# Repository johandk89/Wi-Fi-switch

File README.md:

# ESP8266 Wi-Fi plug
ESP8266 Wi-Fi plug eagle schematic

##Overview
This is the intial design of a ESP8266 relay switch. 
The ESP will draw its power from a 220v to 5v power module (Still need to find the perfect one)
This relay switch is heavliy based on : 

###Parts list
1 x ESP8266 E01
1 x Relay
2 x R1 Resistor
1 x LED
1 x Transistor
1 x Resistor

###License
The MIT License (MIT)

Copyright (c) 2015 johandk89

Permission is hereby granted, free of charge, to any person obtaining a copy
of this software and associated documentation files (the "Software"), to deal
in the Software without restriction, including without limitation the rights
to use, copy, modify, merge, publish, distribute, sublicense, and/or sell
copies of the Software, and to permit persons to whom the Software is
furnished to do so, subject to the following conditions:

The above copyright notice and this permission notice shall be included in all
copies or substantial portions of the Software.

THE SOFTWARE IS PROVIDED "AS IS", WITHOUT WARRANTY OF ANY KIND, EXPRESS OR
IMPLIED, INCLUDING BUT NOT LIMITED TO THE WARRANTIES OF MERCHANTABILITY,
FITNESS FOR A PARTICULAR PURPOSE AND NONINFRINGEMENT. IN NO EVENT SHALL THE
AUTHORS OR COPYRIGHT HOLDERS BE LIABLE FOR ANY CLAIM, DAMAGES OR OTHER
LIABILITY, WHETHER IN AN ACTION OF CONTRACT, TORT OR OTHERWISE, ARISING FROM,
OUT OF OR IN CONNECTION WITH THE SOFTWARE OR THE USE OR OTHER DEALINGS IN THE
SOFTWARE.

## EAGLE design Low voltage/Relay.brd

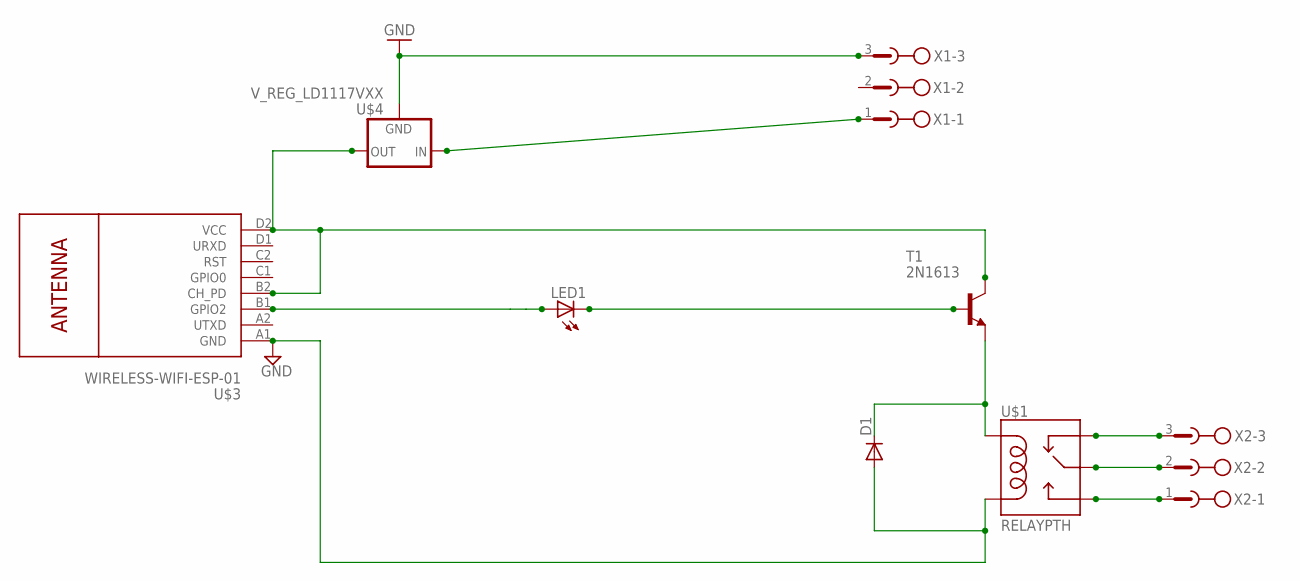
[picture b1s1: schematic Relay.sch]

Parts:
D1: DIODE-D-2.5; D-2.5
LED1: LED3MM
T1: 2N1613; TO5
U$1: RELAYPTH; SRD-05VDC-SL-C
U$3: WIRELESS-WIFI-ESP-01
U$4: V_REG_LD1117VXX; 78XXL
X1, X2: W232-3

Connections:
GND: D1.A, U$1.COIL0, U$3.A1 (GND), U$4.IN (GND), X1.3
unnamed: T1.3 (C), U$3.B2 (CH_PD), U$3.D2 (VCC), U$4.GND (OUT)
unnamed: LED1.A, U$3.B1 (GPIO2)
unnamed: U$4.OUT (IN), X1.1
unnamed: LED1.K (C), T1.2 (B)
unnamed: U$1.SWCLOSED (SWCLOSE), X2.3
unnamed: D1.C, T1.1 (E), U$1.COIL1
unnamed: U$1.SWCOMMON, X2.2
unnamed: U$1.SWOPEN, X2.1

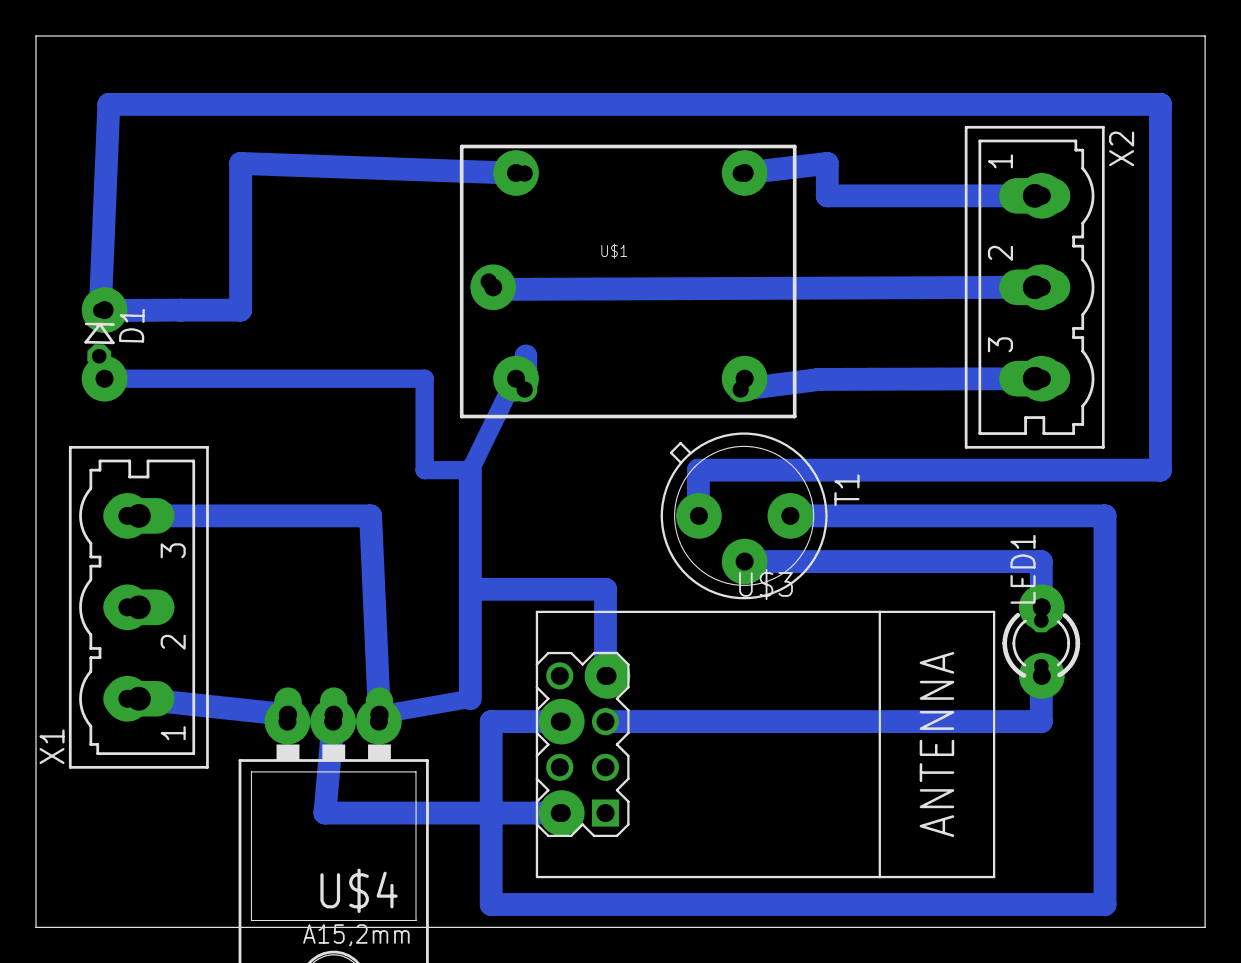
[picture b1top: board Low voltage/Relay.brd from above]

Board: 2 copper layers, 65.0 x 49.5 mm, 8 parts (0 on the bottom side), 9 nets.

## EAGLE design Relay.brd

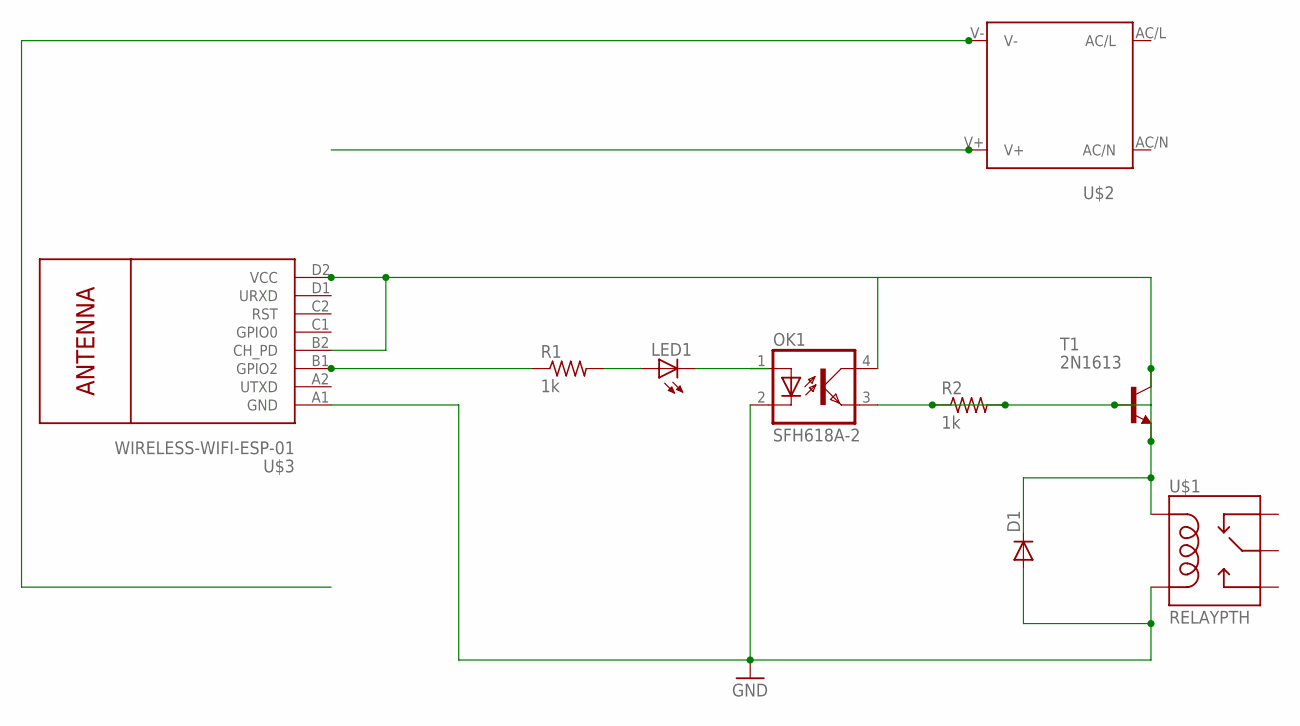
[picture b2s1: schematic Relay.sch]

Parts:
D1: DIODE-D-2.5; D-2.5
LED1: LED3MM
OK1: SFH618A-2; DIP4
R1, R2: 1k; R2012
T1: 2N1613; TO5
U$1: RELAYPTH; SRD-05VDC-SL-C
U$2: IRM_15/20
U$3: WIRELESS-WIFI-ESP-01

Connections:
GND: D1.A, OK1.2 (C), U$1.COIL0, U$3.A1 (GND)
unnamed: R1.1, U$3.B1 (GPIO2)
unnamed: LED1.A, R1.2
unnamed: D1.C, OK1.3 (EMIT), OK1.4 (COL), R2.1, R2.2, T1.1 (E), T1.2 (B), T1.3 (C), U$1.COIL1, U$3.B2 (CH_PD), U$3.D2 (VCC)

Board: 2 copper layers, 9 parts (0 on the bottom side), 4 nets, no tracks yet.

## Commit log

2015-03-19 Added readme and sorted project
2015-05-09 Add low voltage
2015-05-09 board layout
2015-05-09 Added board Via
2015-05-09 SAve file
2015-05-11 Added Low voltage PDF

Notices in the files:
parts and their libraries:
diy-modules: Released under the Creative Commons Attribution 4.0 International License: http://creativecommons.org/licenses/by/4.0
SparkFun-PowerIC: Licensing: Creative Commons ShareAlike 4.0 International - https://creativecommons.org/licenses/by-sa/4.0
